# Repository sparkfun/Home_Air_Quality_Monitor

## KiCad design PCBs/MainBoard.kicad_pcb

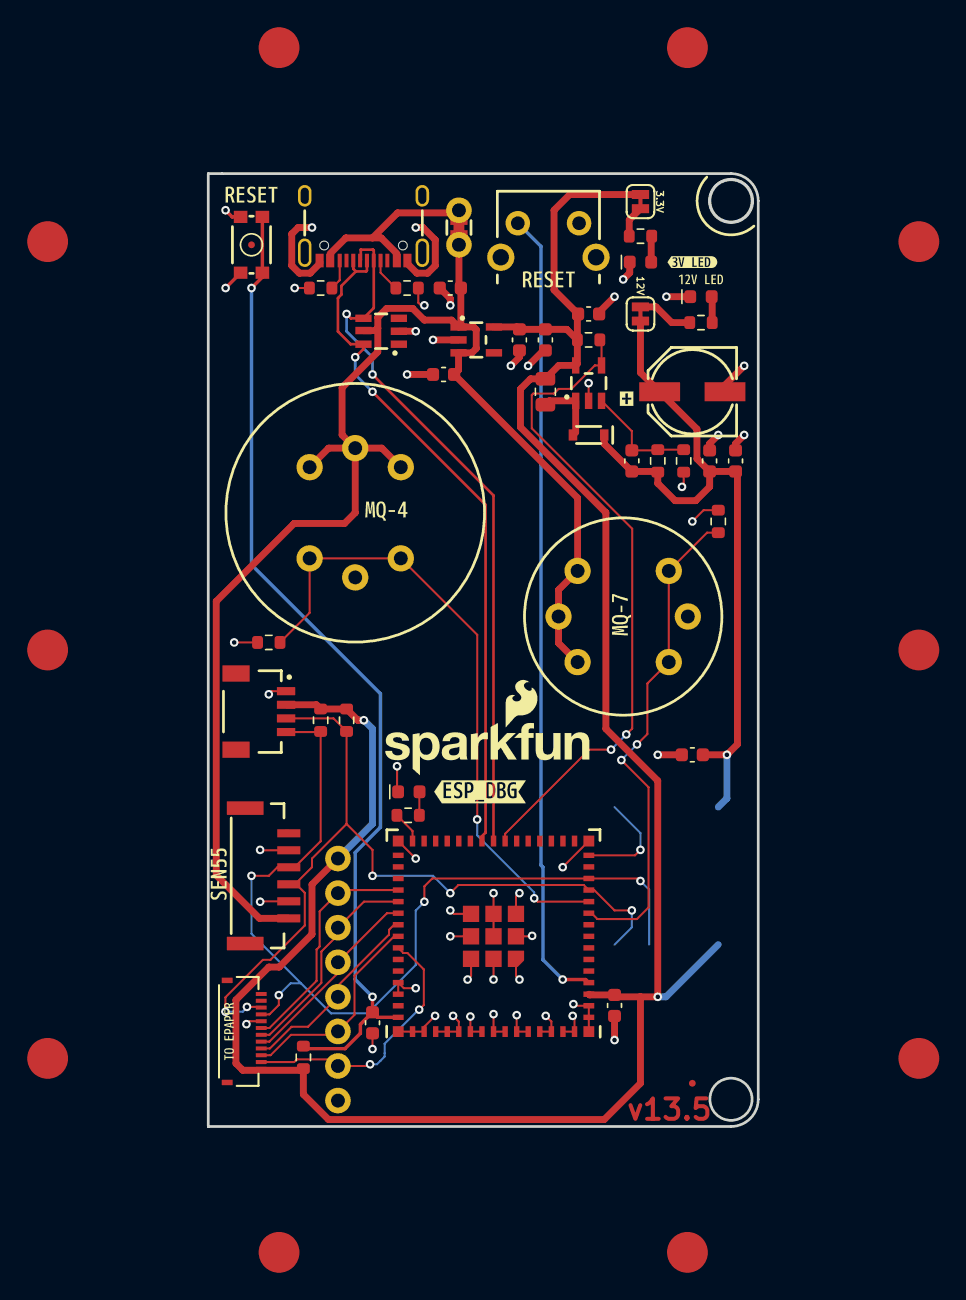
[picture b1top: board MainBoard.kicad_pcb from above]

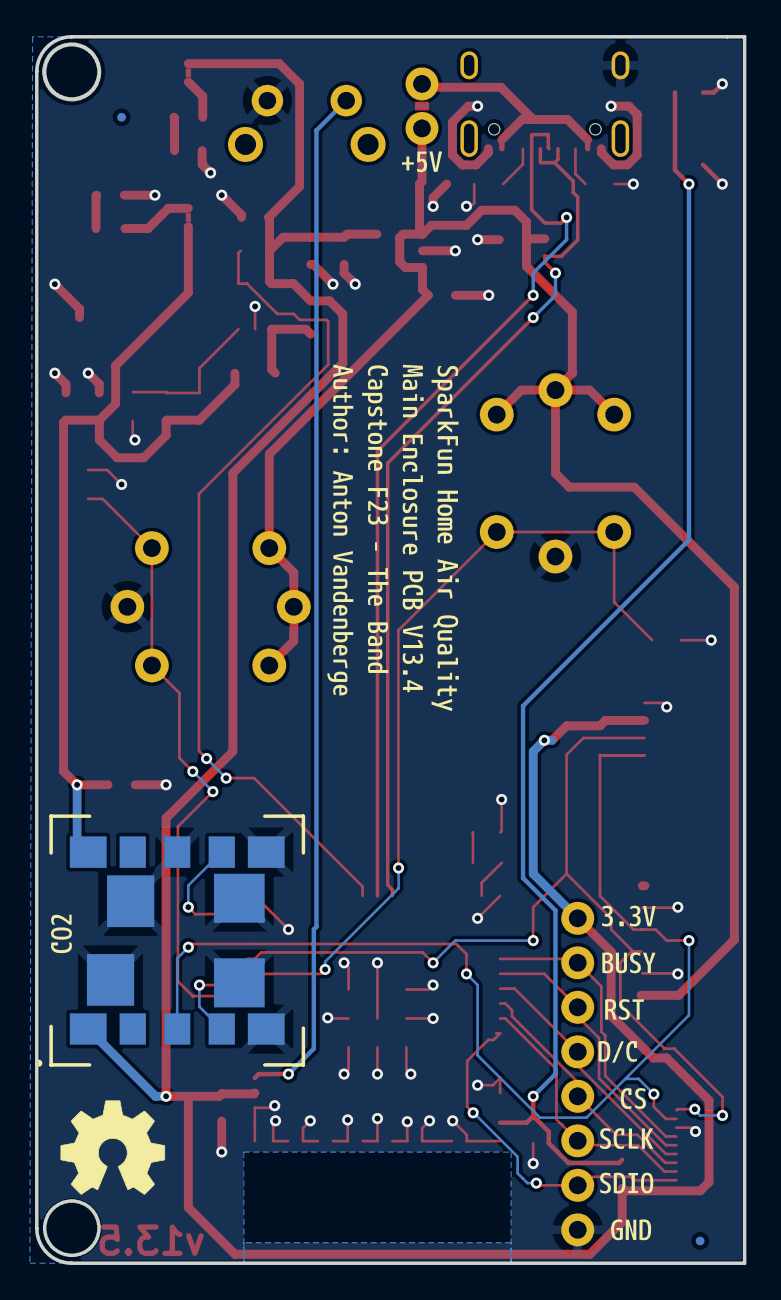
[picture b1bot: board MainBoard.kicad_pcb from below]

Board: 2 copper layers, 40.4 x 70.0 mm, 85 parts (13 on the bottom side), 31 nets.

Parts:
C1, C2, C3, C8: 0.1uF; C_0603_1608Metric
C4, C12: 10uF; C_0603_1608Metric
C5: 470pF; C_0603_1608Metric
C6: 4.7uF; C_0603_1608Metric
C7: 47uF; PANASONIC_D
C9: 10nF; C_0603_1608Metric
C10, C11: 1.0uF; C_0603_1608Metric
D1: 0.5A; SOD-323
D2, D3, D4: Red; LED_0603_1608Metric
FID1, FID2, FID3, FID4: Fiducial_0.5mm; Fiducial_0.5mm_Mask1mm
FID5, FID6, FID7, FID8, FID9, FID10, FID11, FID12, FID13, FID14: Fiducial_3mm; Fiducial_1.5mm_Mask3mm
G1: OSHW_Logo; Creative_Commons_License
J1: USB_C_Receptacle; USB-C-16P
J2: Conn_01x12_FPC_0.5mm; FPC_12_0.5MM
J3: Conn_01x08; 1X08
J4: Qwiic_RA; JST04_1MM_RA
JP1: Measure; COMBO-JUMPER_2_NC_TRACE
JP2, JP3: SMT-JUMPER_2_NC_TRACE_SILK
L1: 10uH; C_0805_2012Metric
R1, R2: 5.1k; R_0603_1608Metric
R3, R7, R9, R11, R12: 10k; R_0603_1608Metric
R4: 100k; R_0603_1608Metric
R5: 47k; R_0603_1608Metric
R6: 5.62k; R_0603_1608Metric
R8, R10: 2.2k; R_0603_1608Metric
R15: 220_0603; R_0603_1608Metric
Ref**: Val**; OSHW_Logo_6mm
ST1: Stand_off; STAND-OFF
SW1: PTH_RA_h7.5mm; Momentary_PTH_RA_8-020_h7.5mm
SW2: SMD_4.6x2.8mm_h2.5mm; Momentary_SMD_4.6x2.8mm_h2.5mm
U1: TVS_ESD_USB; SOT23-6
U2: ESP32-S3-MINI; ESP32-MINI
U3: AP3012; SOT23-5
U4: MQ-4 Gas Sensor
U5: PASCO2V01BUMA1; LG-MLGA-14-1_Z8B00206105
U6: AP2112K-3.3; SOT23-5
U7: MQ-7 Gas Sensor
U8: SEN55; JST-6-SMD-1.25MM-LOCKING
kibuzzard-65B1D3B2: G***; kibuzzard-65B1D3B2
kibuzzard-65B1D5D4: G***; kibuzzard-65B1D5D4
kibuzzard-65B1D5EA: G***; kibuzzard-65B1D5EA
kibuzzard-65B1D56F: G***; kibuzzard-65B1D56F
kibuzzard-65B1D64A: G***; kibuzzard-65B1D64A
kibuzzard-65B1D673: G***; kibuzzard-65B1D673
kibuzzard-65B1DFAF: G***; kibuzzard-65B1DFAF
kibuzzard-65B1E2D2: G***; kibuzzard-65B1E2D2
kibuzzard-65B1E2FB: G***; kibuzzard-65B1E2FB
kibuzzard-65B1E10A: G***; kibuzzard-65B1E10A
kibuzzard-65B1E11D: G***; kibuzzard-65B1E11D
kibuzzard-65B1E12C: G***; kibuzzard-65B1E12C
kibuzzard-65B1E13C: G***; kibuzzard-65B1E13C
kibuzzard-65B1E14E: G***; kibuzzard-65B1E14E
kibuzzard-65B1E16C: G***; kibuzzard-65B1E16C
kibuzzard-65B1E40B: G***; kibuzzard-65B1E40B
kibuzzard-65B1E160: G***; kibuzzard-65B1E160
kibuzzard-65B1E179: G***; kibuzzard-65B1E179
kibuzzard-65B27CA0: G***; kibuzzard-65B27CA0
kibuzzard-65ECB56E: G***; kibuzzard-65ECB56E
kibuzzard-65F1350E: G***; kibuzzard-65F1350E

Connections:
+3.3V: C3.1, C4.1, C11.1, C12.1, J2.12, J3.1, J4.2, JP3.2 (B), L1.1, R3.1, R4.2, R8.1, R10.1, U2.3 (3V3), U3.5 (IN), U5.1 (3V3), U6.5 (VOUT)
+5V: C2.1, C10.1, JP1.2 (B), U1.5 (VCC), U4.1 (5V), U4.2 (H+), U4.3 (5V), U6.1 (VIN), U6.3 (EN), U7.1 (5V), U7.2 (H+), U7.3 (5V), U8.6 (VDD)
+12V: C5.1, C6.1, C7.+, C8.1, C9.1, D1.C, JP2.2 (B), R5.1, U5.10 (12V)
CO2_INT: U2.15 (IOA11), U5.7 (INT)
D+: J1.A6 (D+), J1.B6 (D+), U1.6 (I/O4), U2.24 (IOA20)
D-: J1.A7 (D-), J1.B7 (D-), U1.4 (I/O3), U2.23 (IOA19)
D/~C: J2.9, J3.5, U2.37 (IO41)
ESP0: SW1.2 (B), U2.4 (IO0)
ESP10/MQ7: R11.1, U2.10 (IOA6), U7.4 (SENSE-GND), U7.6 (SENSE-GND)
ESP11/MQ4: R7.1, U2.11 (IOA7), U4.4 (SENSE-GND), U4.6 (SENSE-GND)
ESP DBG: R15.1, U2.30 (IO48)
GND: C1.1, C2.2, C3.2, C4.2, C6.2, C7.-, C8.2, C9.2, C10.2, C11.2, C12.2, D2.1 (K), D3.1 (K), D4.1 (K), J1.GND, J1.S (SHIELD), J2.5, J3.8, J4.1, R1.2, R2.2, R6.2, R7.2, R11.2, SW1.1 (A), SW2.1 (A), U1.2 (GND), U2.1 (GND), U2.2 (GND), U2.42 (GND), U2.43 (GND), U2.46 (GND), U2.47 (GND), U2.48 (GND), U2.49 (GND), U2.50 (GND), U2.51 (GND), U2.52 (GND), U2.53 (GND), U2.54 (GND), U2.55 (GND), U2.56 (GND), U2.57 (GND), U2.58 (GND), U2.59 (GND), U2.60 (GND), U2.61 (GND), U2.62 (GND), U2.63 (GND), U2.64 (GND), U2.65 (GND), U3.2 (GND), U4.5 (H-), U5.5 (PWM_DIS), U5.6 (GND), U5.8 (PSEL), U5.11 (GND), U5.12 (GND), U5.13 (GND), U5.14 (GND), U6.2 (GND), U7.5 (H-), U8.2 (SEL), U8.5 (GND)
unnamed: D2.2 (A), R9.2
unnamed: D3.2 (A), R12.2
unnamed: D4.2 (A), R15.2
unnamed: J1.A5 (CC1), R2.1
unnamed: J1.B5 (CC2), R1.1
unnamed: J1.VBUS, JP1.1 (A)
unnamed: JP2.1 (A), R9.1
unnamed: JP3.1 (A), R12.1
unnamed: C5.2, R5.2, R6.1, U3.3 (FB)
unnamed: D1.A, L1.2, U3.1 (SW)
RESET: C1.2, R3.2, SW2.2 (B), U2.45 (EN)
SCL: J2.4, J4.4, R8.2, U2.13 (IOA9), U5.3 (SCL), U8.3 (SCL)
SCLK: J2.7, J3.3, U2.35 (IO39)
SDA: J2.3, J4.3, R10.2, U2.12 (IOA8), U5.4 (SDA/TX), U8.4 (SDA)
SDIO: J2.6, J3.2, U2.34 (IO38)
~BUSY: J2.11, J3.7, U2.39 (TXD0/IO43)
~CS: J2.8, J3.4, U2.36 (IO40)
~RST: J2.10, J3.6, U2.38 (IO42)
~SHDN-EN: R4.1, U2.22 (IOA18), U3.4 (~SHDN)

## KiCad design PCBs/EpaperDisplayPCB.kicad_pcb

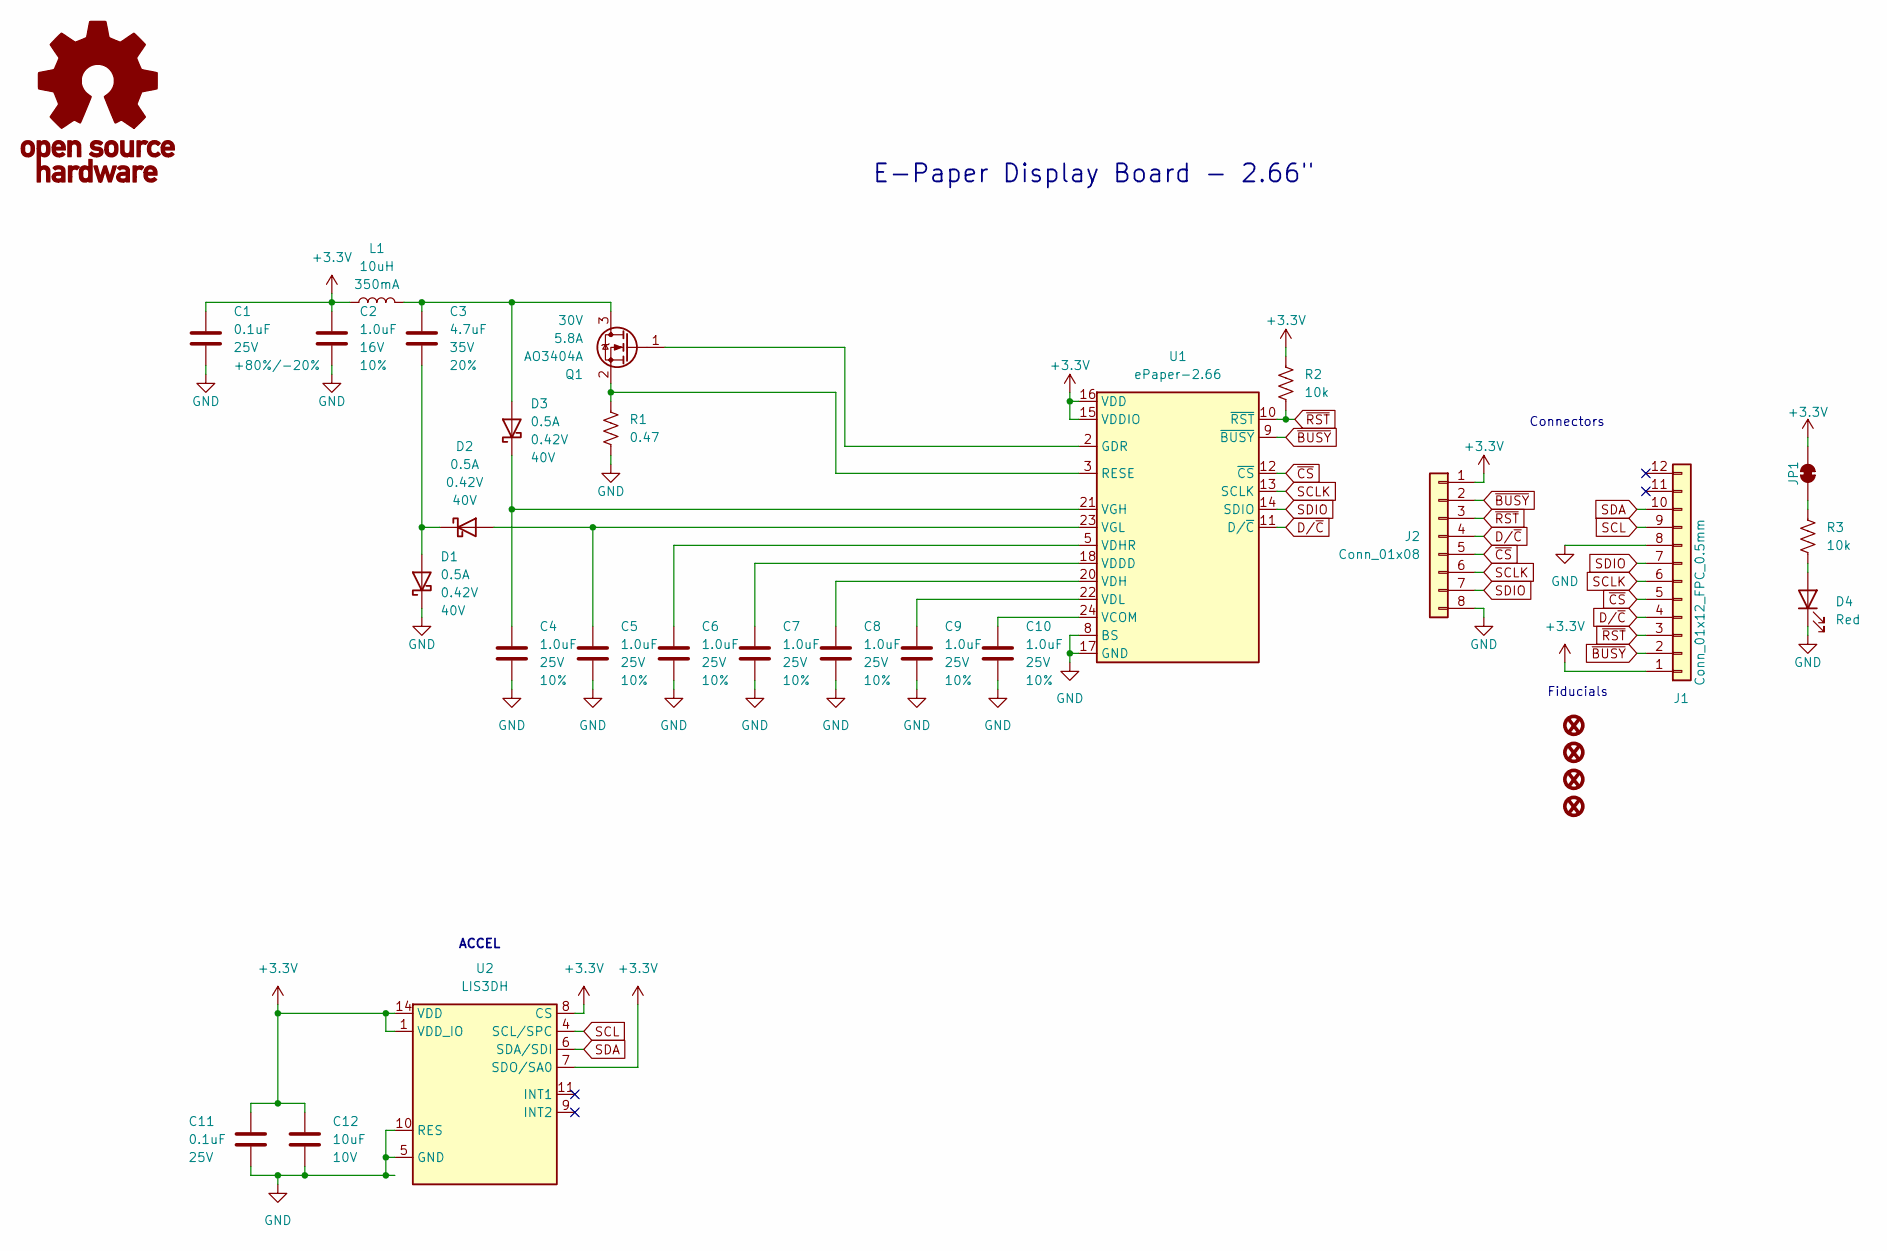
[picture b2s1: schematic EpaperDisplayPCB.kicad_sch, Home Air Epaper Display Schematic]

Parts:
C1, C11: 0.1uF; C_0603_1608Metric; Voltage 25V; Tolerance +80%/-20%
C2: 1.0uF; C_0603_1608Metric; Voltage 16V; Tolerance 10%
C3: 4.7uF; C_0603_1608Metric; Voltage 35V; Tolerance 20%
C4, C5, C6, C7, C8, C9, C10: 1.0uF; C_0805_2012Metric; Voltage 25V; Tolerance 10%
C12: 10uF; C_0603_1608Metric; Voltage 10V; Tolerance 20%
D1, D2, D3: 0.5A; SOD-323
D4: Red; LED_0603_1608Metric
FID1, FID2, FID3, FID4: Fiducial_0.5mm; Fiducial_0.5mm_Mask1mm
G1: OSHW_Logo; Creative_Commons_License
J1: Conn_01x12_FPC_0.5mm; FPC_12_0.5MM
J2: Conn_01x08; 1X08
JP1: SMT-JUMPER_2_NC_TRACE_SILK
L1: 10uH; C_0805_2012Metric
Q1: AO3404A; SOT23-3
R1: 0.47; R_0603_1608Metric
R2, R3: 10k; R_0603_1608Metric
U1: ePaper-2.66
U2: LIS3DH; LGA-16_3x3mm_P0.5mm_LayoutBorder3x5y

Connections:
+3.3V: C1.1, C2.1, C11.1, C12.1, J1.1, J2.1, JP1.2 (B), L1.1, R2.1, U1.15 (VDDIO), U1.16 (VDD), U2.1 (VDD_IO), U2.7 (SDO/SA0), U2.8 (CS), U2.14 (VDD)
D/~C: J1.4, J2.4, U1.11 (D/~C)
GND: C1.2, C2.2, C4.2, C5.2, C6.2, C7.2, C8.2, C9.2, C10.2, C11.2, C12.2, D1.C, D4.1 (K), J1.8, J2.8, R1.1, U1.8 (BS), U1.17 (GND), U2.5 (GND), U2.10 (RES), U2.12 (GND)
unnamed: C3.2, D1.A, D2.C
unnamed: D4.2 (A), R3.1
unnamed: JP1.1 (A), R3.2
unnamed: C3.1, D3.A, L1.2, Q1.3 (D)
unnamed: Q1.1 (G), U1.2 (GDR)
unnamed: Q1.2 (S), R1.2, U1.3 (RESE)
unnamed: C10.1, U1.24 (VCOM)
unnamed: C7.1, U1.18 (VDDD)
unnamed: C8.1, U1.20 (VDH)
unnamed: C6.1, U1.5 (VDHR)
unnamed: C9.1, U1.22 (VDL)
unnamed: C4.1, D3.C, U1.21 (VGH)
unnamed: C5.1, D2.A, U1.23 (VGL)
SCL: J1.9, U2.4 (SCL/SPC)
SCLK: J1.6, J2.6, U1.13 (SCLK)
SDA: J1.10, U2.6 (SDA/SDI)
SDIO: J1.7, J2.7, U1.14 (SDIO)
~BUSY: J1.2, J2.2, U1.9 (~BUSY)
~CS: J1.5, J2.5, U1.12 (~CS)
~RST: J1.3, J2.3, R2.2, U1.10 (~RST)

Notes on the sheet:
Fiducials
E-Paper Display Board - 2.66"
ACCEL
Connectors

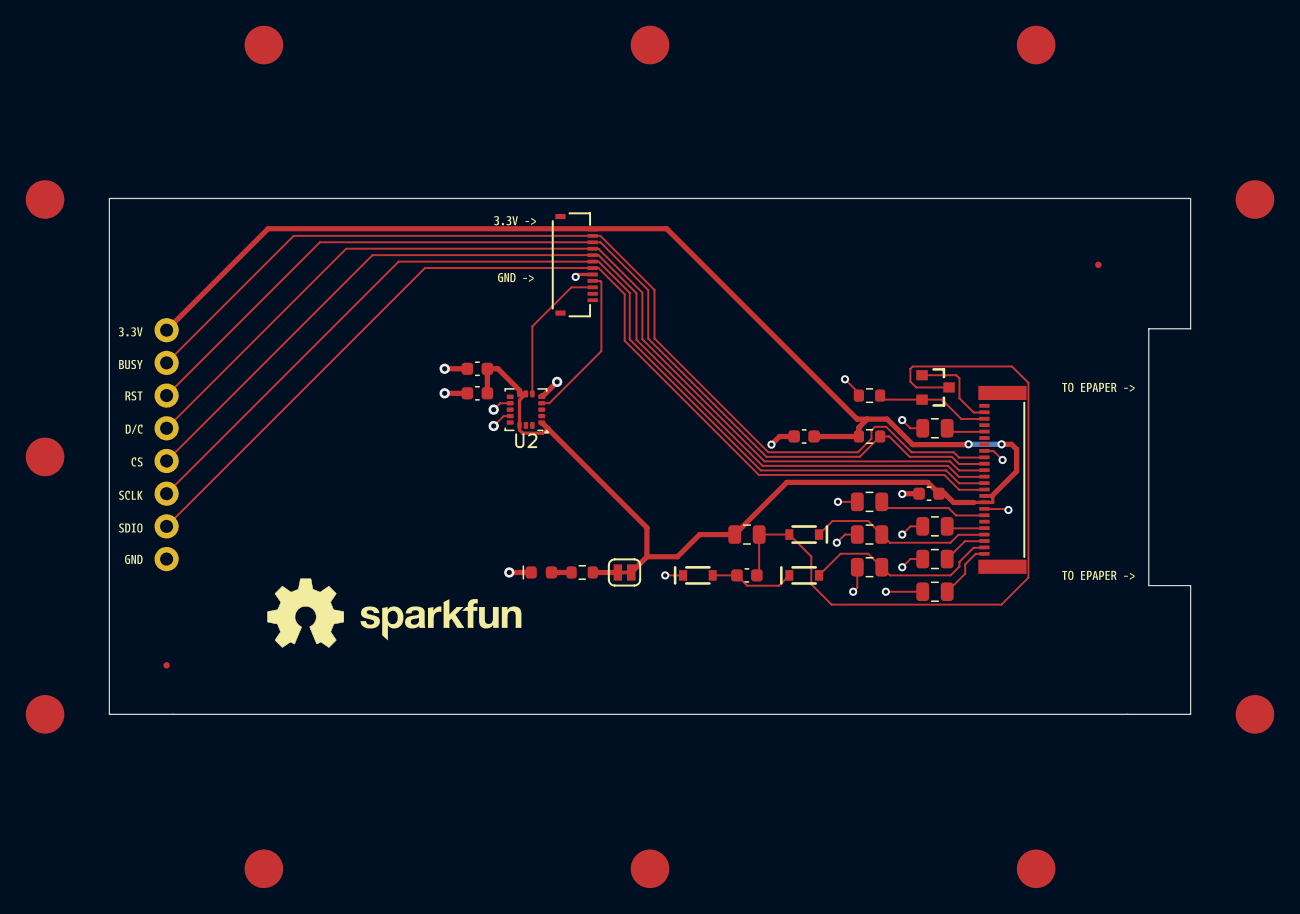
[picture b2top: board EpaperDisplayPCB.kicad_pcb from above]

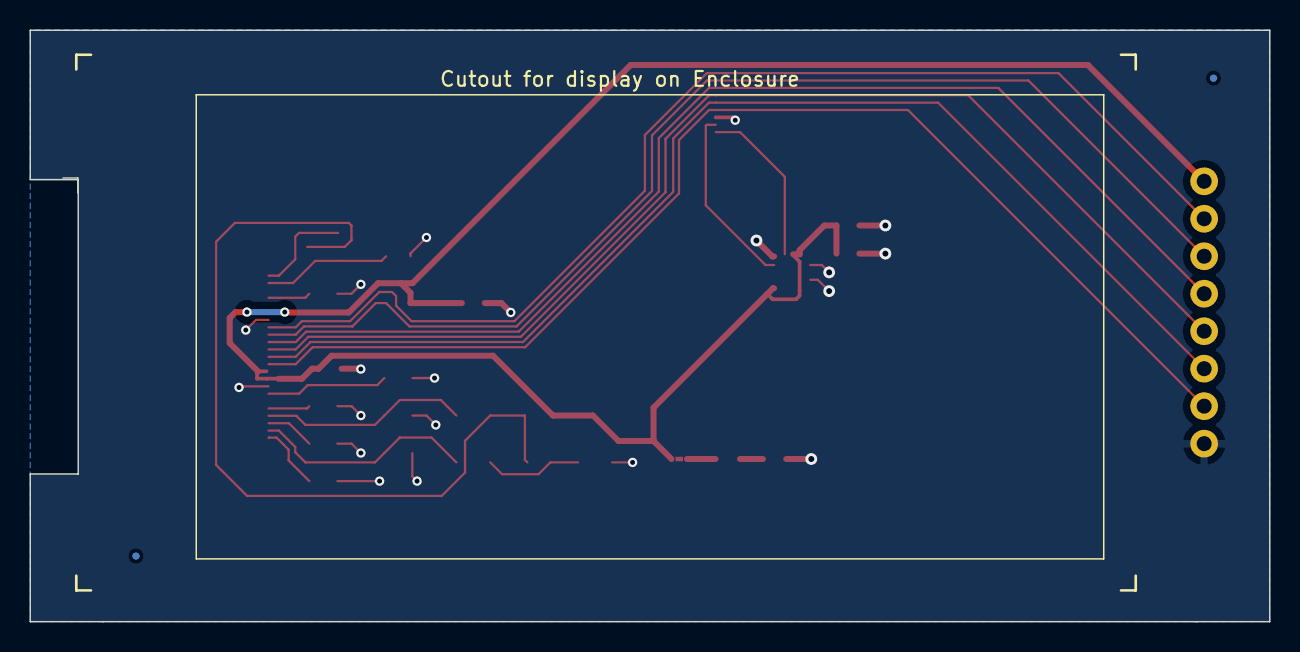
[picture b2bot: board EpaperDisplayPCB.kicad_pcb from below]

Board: 2 copper layers, 84.0 x 40.1 mm, 55 parts (2 on the bottom side), 23 nets.

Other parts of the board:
FID5, FID6, FID7, FID8, FID9, FID10, FID11, FID12, FID13, FID14, FID15: Fiducial_3mm; Fiducial_1.5mm_Mask3mm
Ref**: Val**; OSHW_Logo_6mm
kibuzzard-65B1FFD4: G***; kibuzzard-65B1FFD4
kibuzzard-65B1FFE5: G***; kibuzzard-65B1FFE5
kibuzzard-65B200B7, kibuzzard-65B200B7#2: G***; kibuzzard-65B200B7
kibuzzard-65B2004E: G***; kibuzzard-65B2004E
kibuzzard-65B2005D: G***; kibuzzard-65B2005D
kibuzzard-65B2006B: G***; kibuzzard-65B2006B
kibuzzard-65B20022: G***; kibuzzard-65B20022
kibuzzard-65B20037: G***; kibuzzard-65B20037
kibuzzard-65B20040: G***; kibuzzard-65B20040
kibuzzard-65E131AD: G***; kibuzzard-65E131AD
kibuzzard-65E131D6: G***; kibuzzard-65E131D6

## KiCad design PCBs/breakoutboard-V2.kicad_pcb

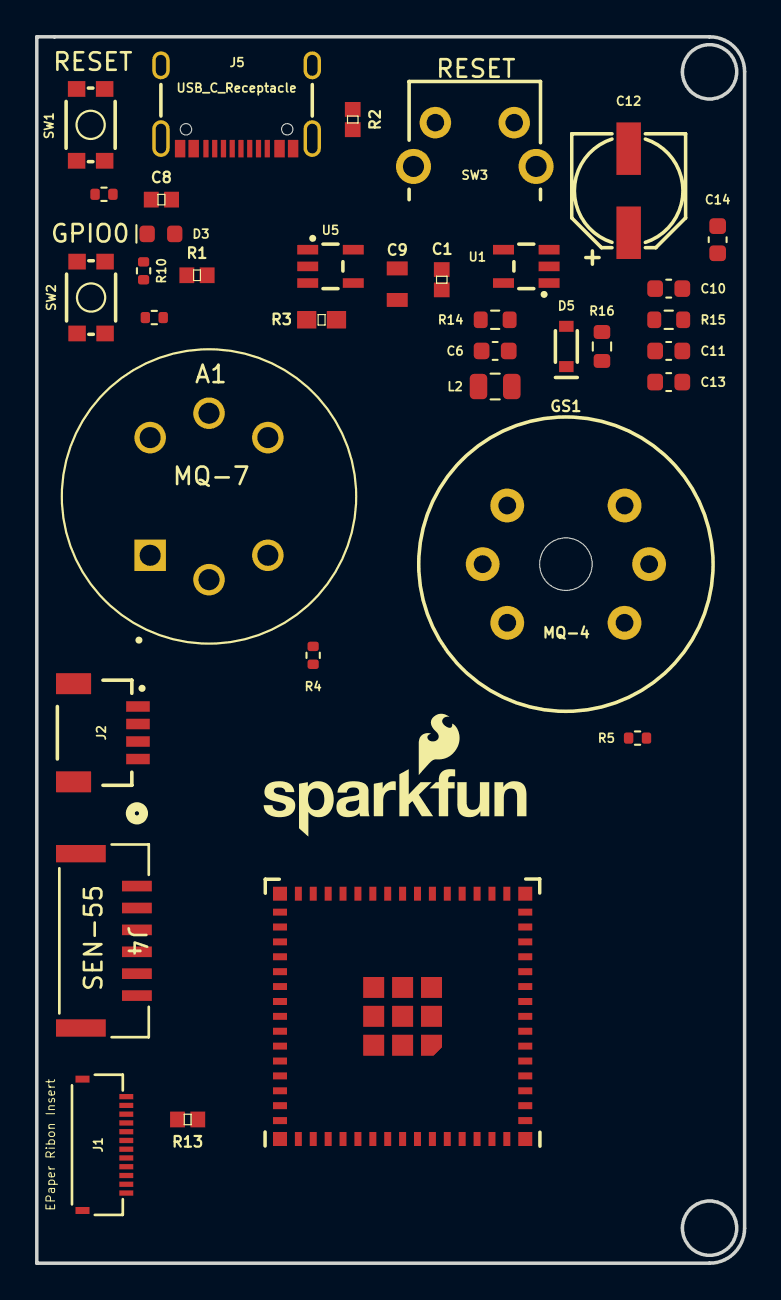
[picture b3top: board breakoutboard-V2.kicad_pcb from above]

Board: 2 copper layers, 40.4 x 70.0 mm, 38 parts (1 on the bottom side), 28 nets, no tracks yet.

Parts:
A1: MQ-7; XDCR_MQ-7
C1: 1.0UF-0402-16V-10%; 0402
C6: 10uF; C_0603_1608Metric
C8: 0.1UF-0402-16V-10%; 0402
C9: 10UF-0805-10V-10%; 0805
C10: 470pF; C_0603_1608Metric
C11: 4.7uF; C_0603_1608Metric
C12: 47uF; PANASONIC_D
C13: 0.1uF; C_0603_1608Metric
C14: 10nF; C_0603_1608Metric
D3: White; LED_0603_1608Metric
D5: 0.5A; SOD-323
G1: OSHW_Logo; Creative_Commons_License
GS1: MQ-4; GAS_SENSOR
IC1: PASCO2V01BUMA1
J1: Conn_01x12_FPC_0.5mm; FPC_12_0.5MM
J2: Qwiic_RA; JST04_1MM_RA
J4: SM06B-GHS-TB; CONN_SM06B-GHS-TB_JST
J5: USB_C_Receptacle; USB-C-16P
L2: 10uH; C_0805_2012Metric
R1, R2: RESISTOR0402-5.1k; 0402
R3: 10KOHM-0603-1_10W-1%; 0603
R4, R5, R6, R8, R10: 10k; R_0402_1005Metric
R13: RESISTOR0402-120 ohm; 0402
R14: 100k; R_0603_1608Metric
R15: 47k; R_0603_1608Metric
R16: 5.62k; R_0603_1608Metric
SW1, SW2: SMD_4.6x2.8mm_h2.5mm; Momentary_SMD_4.6x2.8mm_h2.5mm
SW3: PTH_RA_h7.5mm; Momentary_PTH_RA_8-020_h7.5mm
U1: AP3012; SOT23-5
U3: ESP32-S3-MINI; ESP32-MINI
U5: AP2112K-3.3; SOT23-5

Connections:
/3.3VOUT: C1.1, C6.1, C9.1, IC1.1 (VDD3.3), J2.2, L2.1, R6.1, R8.1, R13.1, R14.1, U1.5 (IN), U3.3 (3V3), U5.5 (VOUT)
/5V-IN: A1.4 (A), A1.5 (H), A1.6 (A), C8.2, D3.2 (A), GS1.A1, GS1.A2, GS1.HA (H1), J4.1, J5.VBUS, R3.1, U5.1 (VIN)
/12V: C10.1, C11.1, C12.+, C13.1, C14.1, D5.C, IC1.10 (VDD12), R15.1
/BUSY_N(GPIO): J1.2, U3.31 (IO35)
/CSB(GPIO): J1.5, U3.34 (IO38)
/D+: J5.A6 (D+), J5.B6 (D+), U3.24 (IOA20)
/D-: J5.A7 (D-), J5.B7 (D-), U3.23 (IOA19)
/D/C(SPI): J1.6, U3.35 (IO39)
/ESP_0: R8.2, SW2.2 (B), U3.4 (IO0)
/MQ4-DATA: GS1.B1, U3.11 (IOA7)
/MQ7-DATA: A1.1 (B), U3.10 (IOA6)
/RESET: R6.2, SW1.2 (B), SW3.2 (B), U3.45 (EN)
/RST_N(GPIO): J1.7, U3.36 (IO40)
/SCL: IC1.3 (SCL), J2.4, J4.4, U3.13 (IOA9)
/SCL-Epaper(SPI): J1.3, U3.32 (IO36)
/SDA: IC1.4 (TX/_SDA), J2.3, J4.3, U3.12 (IOA8)
/SDA-Epaper(SPI): J1.4, U3.33 (IO37)
/TP_EN: R3.2, U5.3 (EN)
GND: A1.2 (H), C1.2, C6.2, C8.1, C9.2, C11.2, C12.-, C13.2, C14.2, GS1.HB (H2), IC1.6 (GND), IC1.8 (PSEL), J1.8, J2.1, J4.2, J4.5, J5.GND, J5.S (SHIELD), R1.1, R2.1, R4.2, R5.2, R10.1, R16.2, SW1.1 (A), SW2.1 (A), SW3.1 (A), U1.2 (GND), U3.1 (GND), U3.2 (GND), U3.42 (GND), U3.43 (GND), U3.46 (GND), U3.47 (GND), U3.48 (GND), U3.49 (GND), U3.50 (GND), U3.51 (GND), U3.52 (GND), U3.53 (GND), U3.54 (GND), U3.55 (GND), U3.56 (GND), U3.57 (GND), U3.58 (GND), U3.59 (GND), U3.60 (GND), U3.61 (GND), U3.62 (GND), U3.63 (GND), U3.64 (GND), U3.65 (GND), U5.2 (GND)
unnamed: A1.3 (B), R4.1
unnamed: D3.1 (K), R10.2
unnamed: GS1.B2, R5.1
unnamed: J1.1, R13.2
unnamed: J5.A5 (CC1), R2.2
unnamed: J5.B5 (CC2), R1.2
unnamed: C10.2, R15.2, R16.1, U1.3 (FB)
unnamed: D5.A, L2.2, U1.1 (SW)
unnamed: R14.2, U1.4 (~SHDN)

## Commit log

2023-10-26 Current design
    Passing information back to SparkFun as to get the correct sparkfun components that would replace non-SparkFun components
2023-11-03 Initial firmware
2023-11-03 FIle organization
    Creating PCB folder and Fusion-360 folder. Adding Fusion Files for enclosure.
2023-11-03 Adding more Fusion Files
    CAD files for footprint and size of "main" PCB and "E paper display" PCB
2023-11-03 current KiCad Files for main board
    Main board PCB current files. Still needs better connector for Epaper display. Having issues with smart LED library adding footprints to PCB editor.
2023-11-03 Removing note
2023-11-04 Added AQI calculations
2023-11-04 Initial longterm test code
    Storing in SPIFFS with doubles from float16. Saves measurements every 15 seconds
2023-11-06 Start of BLE decoding
2023-11-06 Updated Bottom enclosure
    Added tolerance for screws so they won't scratch a surface. Added inset for sticker on bottom.
2023-11-06 Main PCB Schematic
    Current most up to date schematic PDF design
2023-11-07 Transitioned to NimBLE
2023-11-08 Adding .SCH file
    .SCH file for main board PCB
2023-11-08 Update SPIFFS path to not crash
    Added "/" in front of date path to fix crashing issue.
2023-11-15 First ittr of file upload over BLE
    Needs testing ASAP but it compiles :)
2023-11-15 Added prints for client connections and subscribes
2023-11-16 Getting up to date
2023-11-20 Code Review + ITC
    Made many of the changes pointed out in the code review doc.
    Changed from float16 back to native float for time being - space savings aren't being realized at the moment
    Added flag groups and used them in the implementation for mass file transfer. Testing needs to be done still
2023-11-28 Debugging Notifications and SPIFFS
2023-12-02 Debugging BLE data transmissions
2023-12-05 "working" data transfer
    Fixed ITC and SPIFFS bugs so that mass transfer SHOULD be possible
2023-12-05 Working BLE transfer (200b/s)
2023-12-05 Adding start of UI stuff
2023-12-05 Merge
2023-12-05 Quick update
2023-12-06 Added n-packet reads to BLE buffer
2023-12-07 epaper
2023-12-07 Merging
2023-12-08 Added screen and revised BLE
2023-12-14 Homescreen update
2023-12-14 More App widget stuff
2023-12-14 Download support and code review changes
    Made basic changes with notes from code review and added preliminary support for downloading files from the mobile app.
2023-12-15 Replacing erroneous call to Serial0 with Serial
2023-12-15 Main Board PCB Updates
    Main Board PCB .SCH and .PCB files.
    Missing pin assignment for epaper display. Needs confirmation with Sponsor.
2023-12-15 Adding CAD files
    Top Enclosure design with larger Epaper display. Bottom CAD design files including Right Angle Reset Button
2023-12-15 Updated main board
    Updated connections for Epaper discplay
2023-12-15 Ready for Air Review
    Main Board PCB FILES ready for Schematic and Air Wire Review
2023-12-15 Updated Main Board PCBs
    Updated Main Board PCBs ready for Air Wire Review
2023-12-19 Update Main Board PCB
    Replaced ESP32 WROOM with ESP32 mini. READY FOR AIR WIRE REVIEW :D
2023-12-21 Organizing PCB folder
    Deleting old files and renaming files
2023-12-21 Organizing Fusion CAD files
    Deleting old files and adding new files
2023-12-23 Final Foot print CAD size for Epaper Display PCB
    After print testing, this is the footprint size of the Epaper display that press fits into the top of the enclosure to hold the Epaper display in to place.
2023-12-30 Updates in progress
    Currently running through documentation provided. Home Air Quality Main Board Design Review google sheet for comments and what updates were preformed.
2023-12-30 Added Main Board .PRO file
    Adding current mainboard.pro file to git
2023-12-31 More updates
    Working from google doc review - replaced all net labels with global labels - added debounce capacitors - removed all 0402 components and replaced with 0603 components - line "tidy up" - see google d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
2023-12-31 Update to PCB Ready for air wire review
    updated PCB with changes made to the schematic - assuming no changes needed for schematic file ready for air wire review.
2024-01-03 More BLE buttons
2024-01-03 Working on Epaper Display
    I had to edit the Epaper display .pcb layout a lot but I think that with an extreme amount of reverse CAD work with the test PCB's and the position of the ribon cable, I was able to put the 24 pin co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
2024-01-04 Positioning update
    Position update for edge of board marker for e-paper display footprint.
2024-01-04 Main Board Update
    Fixed ESP0 power rail issue
2024-01-04 Updates From feedback
    Added new MQ sensors and PAS CO2 sensors - Added more from board review notes on google doc
2024-01-06 send bin update
2024-01-07 Commiting before starting BLE OTA
2024-01-08 Making updates
    Making updates from Board Review Google doc
2024-01-11 Working fast update code
2024-01-12 Added features to screen
    Added helper functions for showing the time, getting and printing the MAC address, and some logic on when to show the time
2024-01-12 ota code update 1
2024-01-16 Routing Main Board
    Updated from google drive comments and routed main board PCB
2024-01-16 Update Schematic
    Epaper display schematic partial update
2024-01-18 Adding comments
    Comments added to .sch file
2024-01-19 Updates
    Fixing connections between epaper display board and main board pcbs
2024-01-21 Pushing before ota
2024-01-23 ota working
2024-01-23 Stat button
2024-01-23 stat
2024-01-23 Saving direct method for now
2024-01-25 Main PCB update
    Updated per comments in google doc
2024-01-25 Updates
    Screen PCB updates
2024-01-25 Updated SEN55
    Brought back the SEN55 to the board
2024-01-25 graph updates
2024-01-25 Updated Epaper Display
    Updated Epaper Display with new schematic symbol and placed the correct footprint onto the PCB
2024-02-05 Fixed GPIO printing
2024-02-06 Updated callback
2024-02-08 epaper update
2024-02-08 Main Board PCB update
2024-02-08 Graphing update
2024-02-08 Updated updat command
2024-02-08 Enclosure Assembly
    Fusion 360 assembly file of enclosure and PCBs
2024-02-22 merging epd code
2024-02-27 Updated epapar code
2024-02-27 Minor clarity edit, minor bug fix
2024-02-27 Replaced state with FG calls
2024-02-27 Changed file path on includes
2024-02-27 Fixed compile error
2024-02-27 changed to settings struct
2024-02-27 User Testing 1
2024-02-27 Adding removed files
2024-02-27 Fixed compilation error
2024-02-27 Compiling w/ changes
2024-02-27 Pushing work in epaper driver file
2024-02-27 moved from EPD settings struct to preferences
2024-02-27 small fixes
2024-02-27 Cleaning comments
2024-02-29 trying to push changes again
2024-02-29 Minor updates to OTA and preferences
2024-03-01 Small formatting changes
2024-03-07 working parsing
2024-03-07 Current PCB updates
    Updated Main Board MQ sensors and external reset button position as well as SEN 55 connector pinout.
2024-03-07 Epaper driver updates, icon updates, added icon file folder
2024-03-10 added pairing screen
2024-03-10 fuck you
2024-03-11 Enclosure Updates
2024-03-11 Screen and Main Board Updates
    Updated Main board to Screen PCB connection, added accelerometer to Epaper display PCB. Removed GPIO 0 PB and replaced external Reset button with GPIO0 button.
2024-03-12 Working code
2024-03-13 Minor fixes
2024-03-13 Updated Main Board PCB
    Removed H- resistors to GND from schematic and PCB after confirmed testing that we don't need them.
2024-03-13 Update Main Board V13.4
    Replaced resistor on MQ sensor for resistor that is said to use on data sheet. from 4.7k ohm to 10k ohm.
2024-03-17 Adding updates From review
    Fixed epaper to main board FPC connection.
    Added fiducials to main board for stencil alignment purposes.
2024-03-17 Adding Fiducials to Epaper
    Adding stencil alignment fiducials to epaper PCB
2024-03-19 Working BLE
2024-03-19 Functional indicator
2024-03-21 updating...
2024-03-26 Improved screen functionality
2024-03-26 set code configuration for custom PCB rather than breadboard
2024-03-30 minor updates
2024-03-30 DISC!
2024-04-02 Added sen55 cable drawing in PCB folder, added debugging options in screen driver code
2024-04-05 Adding basic button functionality and minor bug fixes
2024-04-05 Finalizing merge
2024-04-06 Factory reset nearly complete
2024-04-09 Added Enclosure Components
    Added Enclosure Assembly with electronics
2024-04-11 v1.1
2024-04-16 Updated icons
2024-04-16 Fixed bug from previous commit related to 4 digits
2024-04-16 Adding Documentation
2024-04-17 Adding lots
2024-04-18 Epaper updates
2024-04-18 Update sticker
2024-04-20 Adding lots more functionality
2024-04-20 Edits
    Making edits
2024-04-21 Epaper icon updates. Some final polishing and testing still needed. Data upload progress screen added, not tested due to not having phone to connect.
2024-04-21 Nearly final
2024-04-23 fixed unit bug
2024-04-25 New Docs
2024-04-25 docs update
2024-04-25 Deployed 73d794f with MkDocs version: 1.6.0
2024-04-25 Added custom name to EPD
    Introduced a bug on the initial pairing screen due to increased name length
2024-04-26 Added last code needed to rotate screen
2024-04-26 Fixed small bug
2024-04-26 updated pairing screen bitmap
2024-05-01 Near final code

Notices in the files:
parts and their libraries:
Released under the Creative Commons Attribution Share-Alike 4.0 License
https://creativecommons.org/licenses/by-sa/4.0
